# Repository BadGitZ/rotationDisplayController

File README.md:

ATtiny85 based controllerboard for a rotating display stand with RGB-lighting

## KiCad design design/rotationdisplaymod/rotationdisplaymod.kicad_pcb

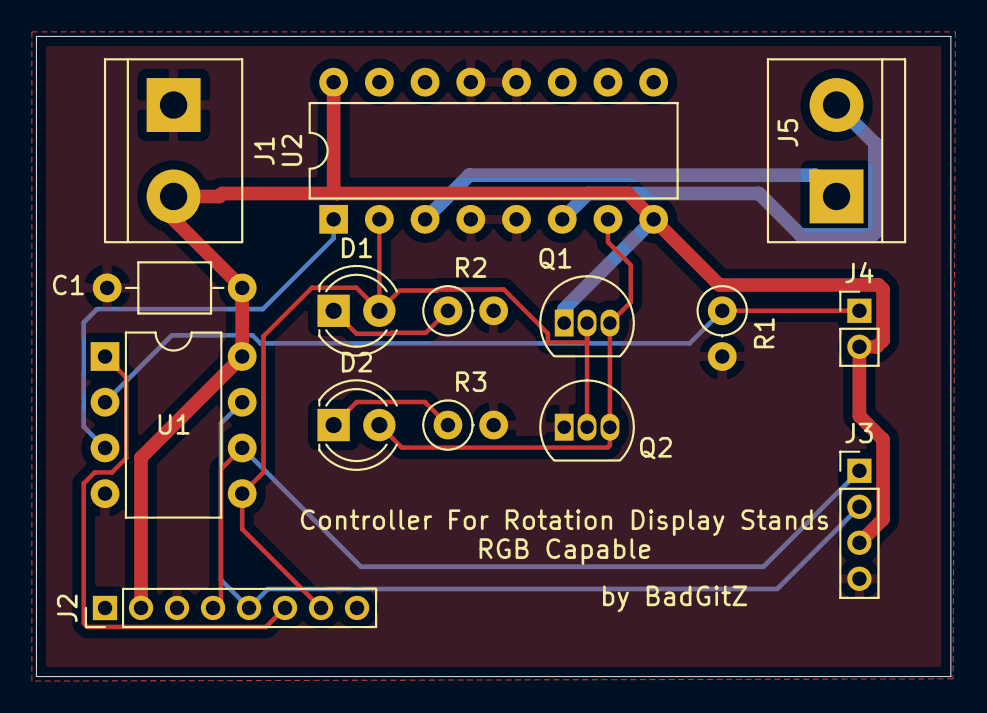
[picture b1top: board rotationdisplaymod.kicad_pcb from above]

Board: 2 copper layers, 50.8 x 35.6 mm, 15 parts (0 on the bottom side), 13 nets.

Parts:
C1: 200nF; C_Axial_L3.8mm_D2.6mm_P7.50mm_Horizontal
D1, D2: LED; LED_D4.0mm
J1: Power_Terminal; TerminalBlock_bornier-2_P5.08mm
J2: Prog_Con; PinHeader_1x08_P2.00mm_Vertical
J3: LED_Con; PinHeader_1x04_P2.00mm_Vertical
J4: Joy_Con; PinHeader_1x02_P2.00mm_Vertical
J5: Motor_Terminal; TerminalBlock_bornier-2_P5.08mm
Q1: BS250; TO-92_Inline
Q2: 2N7000; TO-92_Inline
R1: 1k; R_Axial_DIN0207_L6.3mm_D2.5mm_P2.54mm_Vertical
R2, R3: 22k; R_Axial_DIN0207_L6.3mm_D2.5mm_P2.54mm_Vertical
U1: ATtiny85-20PU; DIP-8_W7.62mm
U2: L293D; DIP-16_W7.62mm

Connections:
/GND: C1.2, J1.1, J2.3, J3.4, Q2.1, R1.2, R2.2, R3.2, U1.4, U2.4, U2.5, U2.12, U2.13
/Motor1: J5.1, U2.3
/Motor2: J5.2, U2.6
/NPin0: D2.2, Q1.3, Q2.3, U2.7
/Pin0: D1.2, J2.7, Q1.2, Q2.2, U1.5, U2.2
/Pin1: J2.4, J3.1, U1.6
/Pin2: J2.5, J3.2, U1.7
/Pin3: J4.1, R1.1, U1.2
/Pin4: U1.3, U2.1
/Reset: J2.6, U1.1
/VCC: C1.1, J1.2, J2.2, J3.3, J4.2, Q1.1, U1.8, U2.8, U2.16
unnamed: D1.1, R2.1
unnamed: D2.1, R3.1

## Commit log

2020-09-08 added new Mplab X project
2020-09-08 deleted old atmel studio project
2020-09-08 prototyped the input processing
2020-09-08 removed makefile
    should probably leave just the source
2020-09-08 removed mplab files
2020-09-08 removed mplab files for real
2020-09-26 first production, kicad
2020-09-27 fixed missing trace
2020-10-26 motorcontrol, led selection, developing on functional hardware
